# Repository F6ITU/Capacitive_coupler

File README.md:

Capcoupler 

Petit coupleur capacitif (ou "tap" en franglais) destiné à prélever une faible portion d'énergie dans un circuit HF de puissance. 

Selon la puissance émise, les condensateurs utilisés doivent être capable de supporter entre 500 et 2000V. Capas porcelaine ou mica "cms" vivement conseillées. Caveat emptor

Comparativement aux coupleurs inductifs ou capacitifs, ce genre de montage est "relativement" indépendant de la fréquence de travail. Il est donc utilisable sans grande déterioration des performances entre 1 et 500 MHz. 

En revanche, on ne peut espérer la moindre directivité... ce n'est pas un réflectomètre.

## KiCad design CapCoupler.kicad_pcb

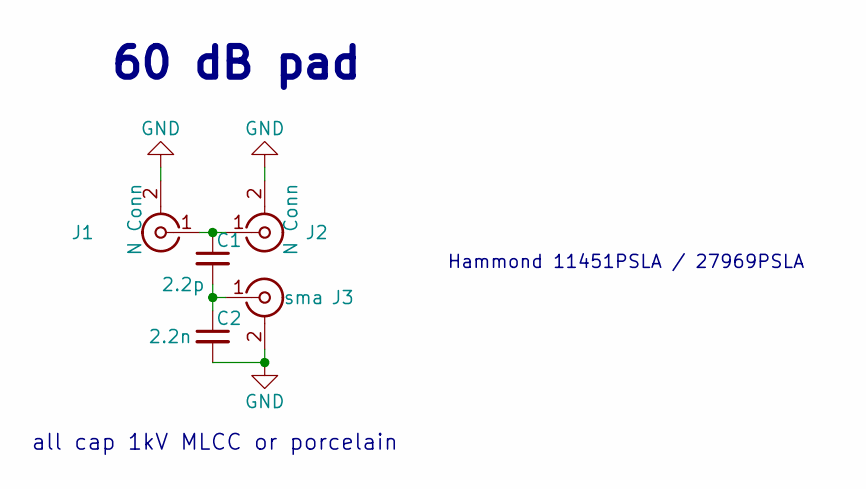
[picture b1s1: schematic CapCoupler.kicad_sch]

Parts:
C1: 2.2p; ATC_500_Dual_HandSoldering
C2: 2.2n; ATC_500_HandSoldering
J1, J2: N Conn; SMA_EDGE_NRW
J3: sma; SMA_EDGE_NRW

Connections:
GND: C2.2, J1.2 (Ext), J2.2 (Ext), J3.2 (Ext)
unnamed: C1.1, J1.1 (In), J2.1 (In)
unnamed: C1.2, C2.1, J3.1 (In)

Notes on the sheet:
60 dB pad
Hammond 11451PSLA / 27969PSLA
all cap 1kV MLCC or porcelain

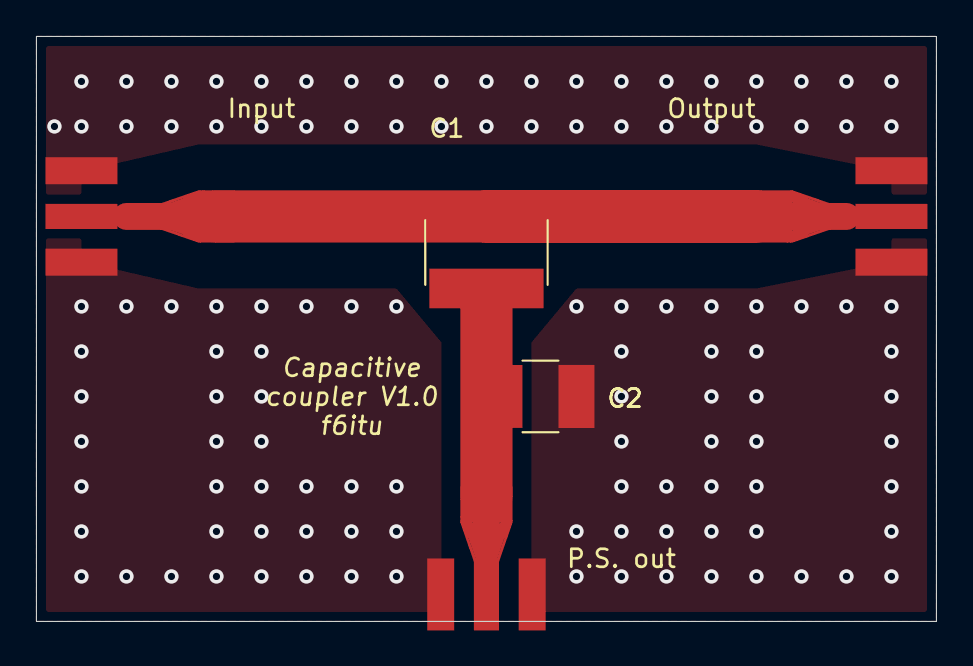
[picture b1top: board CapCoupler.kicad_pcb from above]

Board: 2 copper layers, 50.0 x 32.5 mm, 5 parts (0 on the bottom side), 3 nets.

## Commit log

2024-10-02 first commit of an old and forgotten project
